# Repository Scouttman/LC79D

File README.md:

# LC79D
quectel LC79D breakout board

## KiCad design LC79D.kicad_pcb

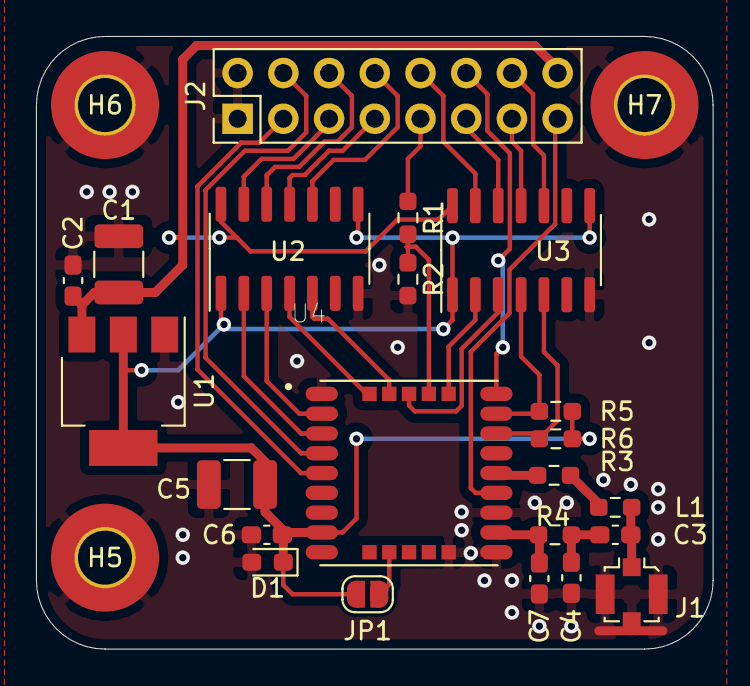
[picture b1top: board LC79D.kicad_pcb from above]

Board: 2 copper layers, 37.6 x 34.0 mm, 25 parts (0 on the bottom side), 32 nets.

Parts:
C1, C5: 10uF; C_1210_3225Metric_Pad1.33x2.70mm_HandSolder
C2, C6: 100nF; C_0603_1608Metric_Pad1.08x0.95mm_HandSolder
C3: 100pF; C_0603_1608Metric_Pad1.08x0.95mm_HandSolder
C4, C7: DNP; C_0603_1608Metric_Pad1.08x0.95mm_HandSolder
D1: DNP; D_0603_1608Metric_Pad1.05x0.95mm_HandSolder
H5, H6, H7: MountingHole_Pad; MountingHole_3mm_Pad_TopBottom
J1: Conn_Coaxial_Power; U.FL_Molex_MCRF_73412-0110_Vertical
J2: Conn_02x08_Odd_Even; PinHeader_2x08_P2.54mm_Vertical
JP1: Jumper_2_Open; SolderJumper-2_P1.3mm_Open_RoundedPad1.0x1.5mm
L1: 68nH; R_0603_1608Metric_Pad0.98x0.95mm_HandSolder
R1, R2, R5, R6: TBD; R_0603_1608Metric_Pad0.98x0.95mm_HandSolder
R3: 10R; R_0603_1608Metric_Pad0.98x0.95mm_HandSolder
R4: 0R; R_0603_1608Metric_Pad0.98x0.95mm_HandSolder
U1: AMS1117-1.8; SOT-223-3_TabPin2
U2, U3: TXB0104D; SOIC-14_3.9x8.7mm_P1.27mm
U4: LC79D; XCVR_LC79D

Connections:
AP_REQ: U3.2, U4.19
AP_REQ_H: J2.10, U3.13
CTS+SPI_MOSI: U2.4, U4.23
CTS+SPI_MOSI_H: J2.7, U2.11
GND: C1.2, C2.2, C4.2, C5.2, C6.2, C7.2, D1.2, H5.1, H6.1, H7.1, J1.2, J2.1, J2.2, R2.2, U1.1, U2.7, U3.7, U4.1, U4.10, U4.12, U4.28
I2C_SCL: R5.1, U3.4, U4.17
I2C_SCL_H: J2.13, U3.11
I2C_SDA: R6.1, U3.5, U4.16
I2C_SDA_H: J2.14, U3.10
INT: J2.12, U4.18
LNA_EN: J2.15, U4.13
unnamed: C3.1, C4.1, R4.1
unnamed: C3.2, J1.1, L1.1
unnamed: JP1.2, U4.25
unnamed: L1.2, R3.2
unnamed: U4.6, U4.7, U4.9, U4.15, U4.24, U4.26, U4.27
PPS: J2.4, U4.4
RDY: R1.2, R2.1, U4.20
RDY_H: J2.9, R1.1
REQ: U3.3, U4.21
REQ_H: J2.11, U3.12
RF_IN: C7.1, R4.2, U4.11
RTS+SPI_MISO: U2.5, U4.22
RTS+SPI_MISO_H: J2.8, U2.10
RXD+SPI_CS: U2.2, U4.3
RXD_SPI_CS_H: J2.5, U2.13
STANDBY: J2.3, U4.5
TXD+SPI_CLK: U2.3, U4.2
TXD+SPI_CLK_H: J2.6, U2.12
VCC: C5.1, C6.1, D1.1, JP1.1, R5.2, R6.2, U1.2, U2.1, U2.8, U3.1, U3.8, U4.8
VCC_RF: R3.1, U4.14
VDD: C1.1, C2.1, J2.16, U1.3, U2.14, U3.14

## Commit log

2021-12-12 breakout board for the LC79D
2021-12-12 added readme
